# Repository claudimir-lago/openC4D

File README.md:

# openC4D
#### _A Capacitively Coupled Contactless Conductivity Detector (C4D) for Capillary Electrophoresis._

To the best of our knowledge, this is still the smallest Capacitively Coupled Contactless Conductivity Detector (C4D) … and it’s open!

Our first C4D was introduced in 1998 [1], and after trials and errors, we published an improved version in 2009 [2]. Here, the continuously improved version is available.

What is here?

•	The plans to build __the printed circuit boards for the detector__ itself. It must be powered, and the signal is available as a digital output in a serial format.

•	__The microcontroller board.__ Although the detector module can be used in a dedicated instrument, this board allows one to control up to four C4Ds through a USB port.

•	__The firmware.__ An Arduino firmware to be used in the microcontroller board.

•	__The frontend.__ A Java frontend to be used to get electropherograms.

We have some papers if you wish to learn more about our CE-C4D [1-8].

1.	da Silva, J.A.F. and C.L. do Lago, An oscillometric detector for capillary electrophoresis. Analytical Chemistry, 1998. 70(20): p. 4339-4343.
2.	Francisco, K.J.M. and C.L. do Lago, A compact and high-resolution version of a capacitively coupled contactless conductivity detector. Electrophoresis, 2009. 30(19): p. 3458-3464.
3.	Brito-Neto, J.G.A., et al., Understanding capacitively coupled contactless conductivity detection in capillary and microchip electrophoresis. Part 1. Fundamentals. Electroanalysis, 2005. 17(13): p. 1198-1206.
4.	Brito-Neto, J.G.A., et al., Understanding capacitively coupled contactless conductivity detection in capillary and microchip electrophoresis. Part 2. Peak shape, stray capacitance, noise, and actual electronics. Electroanalysis, 2005. 17(13): p. 1207-1214.
5.	Francisco, K.J.M. and C.L. do Lago, A capillary electrophoresis system with dual capacitively coupled contactless conductivity detection and electrospray ionization tandem mass spectrometry. Electrophoresis, 2016. 37(12): p. 1718-1724.
6.	Francisco, K.J.M. and C.L. do Lago, Improving thermal control of capillary electrophoresis with mass spectrometry and capacitively coupled contactless conductivity detection by using 3D printed cartridges. Talanta, 2018. 185: p. 37-41.
7.	Saito, R.M., et al., Ionic mobility of the solvated proton and acid-base titration in a four-compartment capillary electrophoresis system. Analytical Methods, 2010. 2(2): p. 164-170.
8.	da Silva, J.A.F., N. Guzman, and C.L. do Lago, Contactless conductivity detection for capillary electrophoresis - Hardware improvements and optimization of the input-signal amplitude and frequency. Journal of Chromatography A, 2002. 942(1-2): p. 249-258.

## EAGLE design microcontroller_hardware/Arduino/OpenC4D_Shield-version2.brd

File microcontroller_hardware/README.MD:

This microcontroller board allows you to connect up to four openC4Ds to an USB port. Then, you can use the [frontend](https://github.com/claudimir-lago/openC4D/tree/master/frontend) for data acquisition or send [Serine commands](https://github.com/claudimir-lago/openC4D/blob/master/firmware/Manual_openC4D_3.pdf) using a [terminal program](https://sites.google.com/site/terminalbpp/).

The original version of the board is based on a [Teensy 2.0 board](https://www.pjrc.com/store/teensy.html), and the one-layer PCB was created in [Eagle](https://www.autodesk.com/products/eagle/free-download). Unfortunately, Teensy 2.0 was discontinued. So, for new projects, consider the Arduino-shield version.

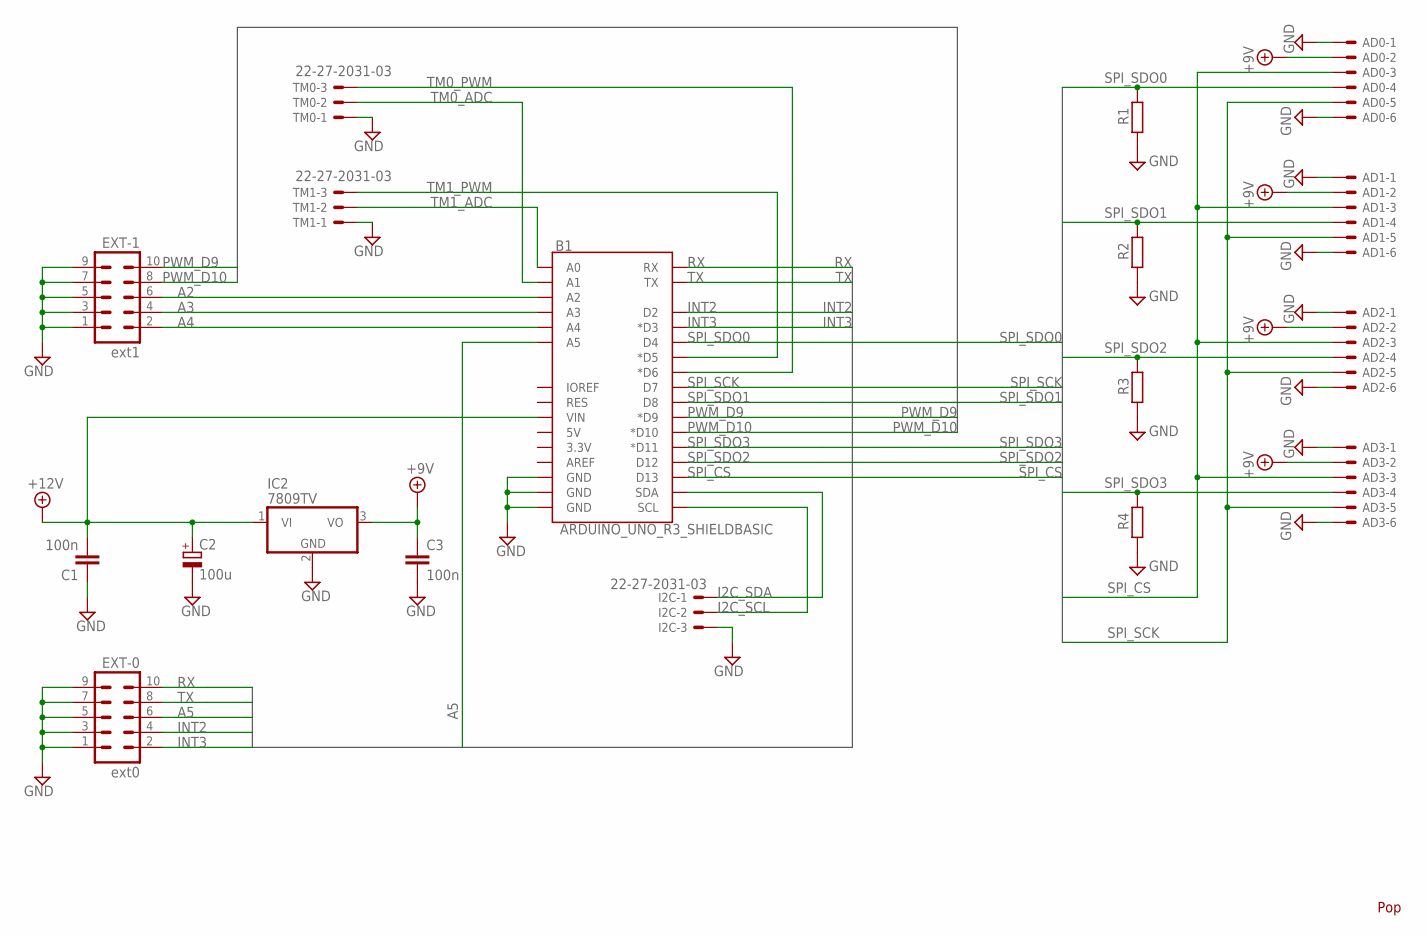
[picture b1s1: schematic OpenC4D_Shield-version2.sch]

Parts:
AD0, AD1, AD2, AD3: 22-27-2061-06; 6410-06
B1: ARDUINO_UNO_R3_SHIELDBASIC; UNO_R3_SHIELD
C1, C3: 100n; C050-025X075
C2: 100u; E3,5-8
EXT-0: ext0; ML10
EXT-1: ext1; ML10
I2C: 22-27-2031-03; 6410-03
IC2: 7809TV; TO220V
R1, R2, R3, R4: R0204/7; 0204/7
TM0, TM1: 22-27-2031-03; 6410-03

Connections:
+9V: AD0.2, AD1.2, AD2.2, AD3.2, C3.1, IC2.3 (VO)
+12V: B1.VIN, C1.2, C2.+, IC2.1 (VI)
A2: B1.A2, EXT-1.6
A3: B1.A3, EXT-1.4
A4: B1.A4, EXT-1.2
A5: B1.A5, EXT-0.6
GND: AD0.1, AD0.6, AD1.1, AD1.6, AD2.1, AD2.6, AD3.1, AD3.6, B1.GND@0 (GND), B1.GND@1 (GND), B1.GND@2 (GND), C1.1, C2.-, C3.2, EXT-0.1, EXT-0.3, EXT-0.5, EXT-0.7, EXT-0.9, EXT-1.1, EXT-1.3, EXT-1.5, EXT-1.7, EXT-1.9, I2C.3, IC2.2 (GND), R1.1, R2.1, R3.1, R4.1, TM0.1, TM1.1
I2C_SCL: B1.SCL, I2C.2
I2C_SDA: B1.SDA, I2C.1
INT2: B1.D2, EXT-0.4
INT3: B1.D3 (*D3), EXT-0.2
PWM_D9: B1.D9 (*D9), EXT-1.10
PWM_D10: B1.D10 (*D10), EXT-1.8
RX: B1.RX, EXT-0.10
SPI_CS: AD0.3, AD1.3, AD2.3, AD3.3, B1.D13
SPI_SCK: AD0.5, AD1.5, AD2.5, AD3.5, B1.D7
SPI_SDO0: AD0.4, B1.D4, R1.2
SPI_SDO1: AD1.4, B1.D8, R2.2
SPI_SDO2: AD2.4, B1.D12, R3.2
SPI_SDO3: AD3.4, B1.D11 (*D11), R4.2
TM0_ADC: B1.A1, TM0.2
TM0_PWM: B1.D6 (*D6), TM0.3
TM1_ADC: B1.A0, TM1.2
TM1_PWM: B1.D5 (*D5), TM1.3
TX: B1.TX, EXT-0.8

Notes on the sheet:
Pop

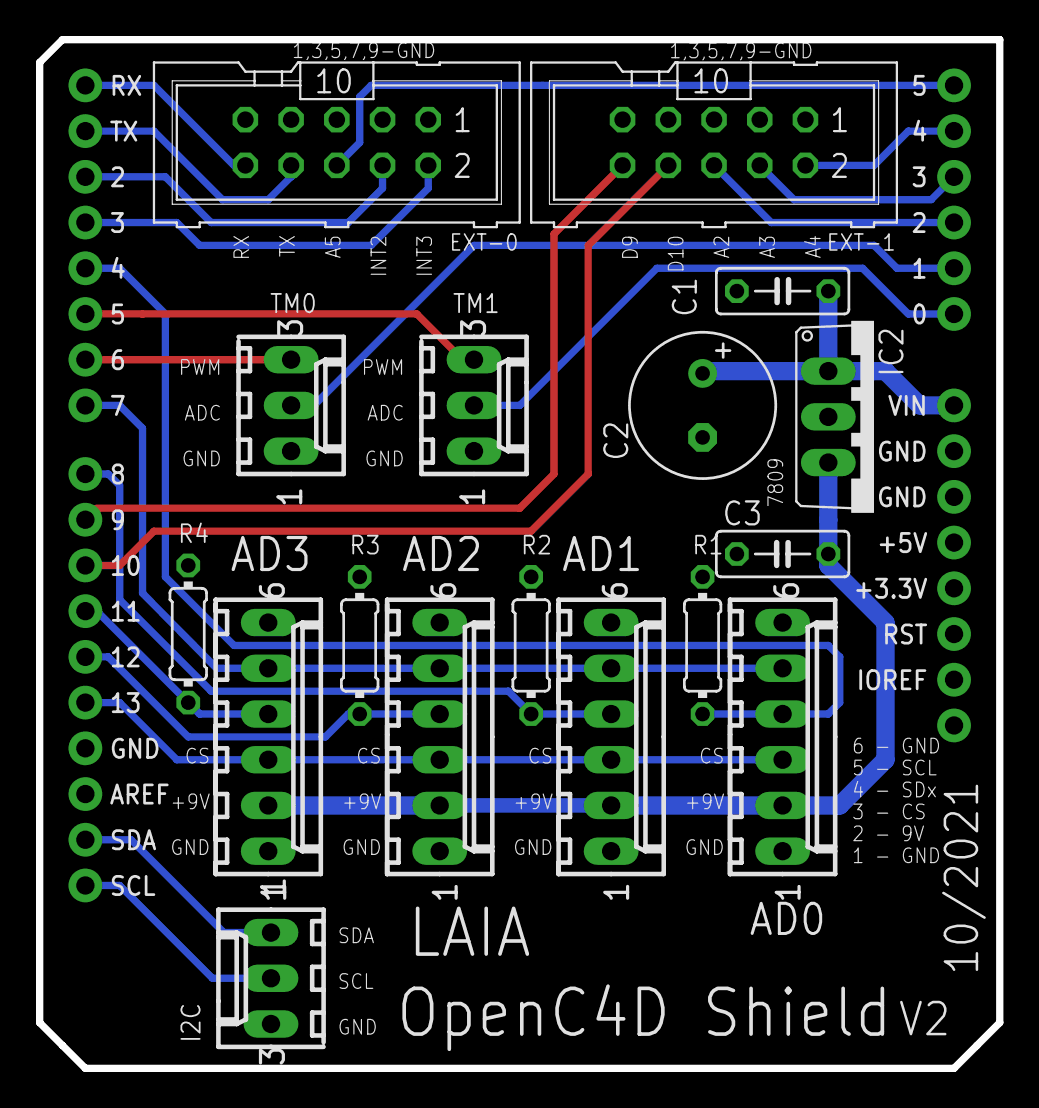
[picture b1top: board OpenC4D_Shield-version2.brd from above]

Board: 2 copper layers, 53.3 x 57.1 mm, 18 parts (0 on the bottom side), 25 nets.

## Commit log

2018-07-25 new stuff
2018-07-27 The hardware
2018-07-27 microcontroller
2018-07-27 Set theme jekyll-theme-cayman
2018-09-26 citation about the libraries
2019-10-30 new figures
    new figures
2019-10-30 new figures
2019-10-31 new C4D hardware
2021-10-28 firmware 4.0 and frontend 1.1
    new versions of firmware (now for Arduino UNO) and frontend (jSSC was uptaded)
2021-10-29 frontend dist
2023-01-26 Teensy version was moved to a folder
2023-01-26 Arduino version

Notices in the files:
parts and their libraries:
SparkFun-Boards: Licensing: Creative Commons ShareAlike 4.0 International - https://creativecommons.org/licenses/by-sa/4.0
